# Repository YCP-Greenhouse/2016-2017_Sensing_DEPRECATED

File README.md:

# Sensing

This archive represents the efforts of the 2016-2017 capstone team.
This archive does not contain designs for the final, deployed version of the sensing system.

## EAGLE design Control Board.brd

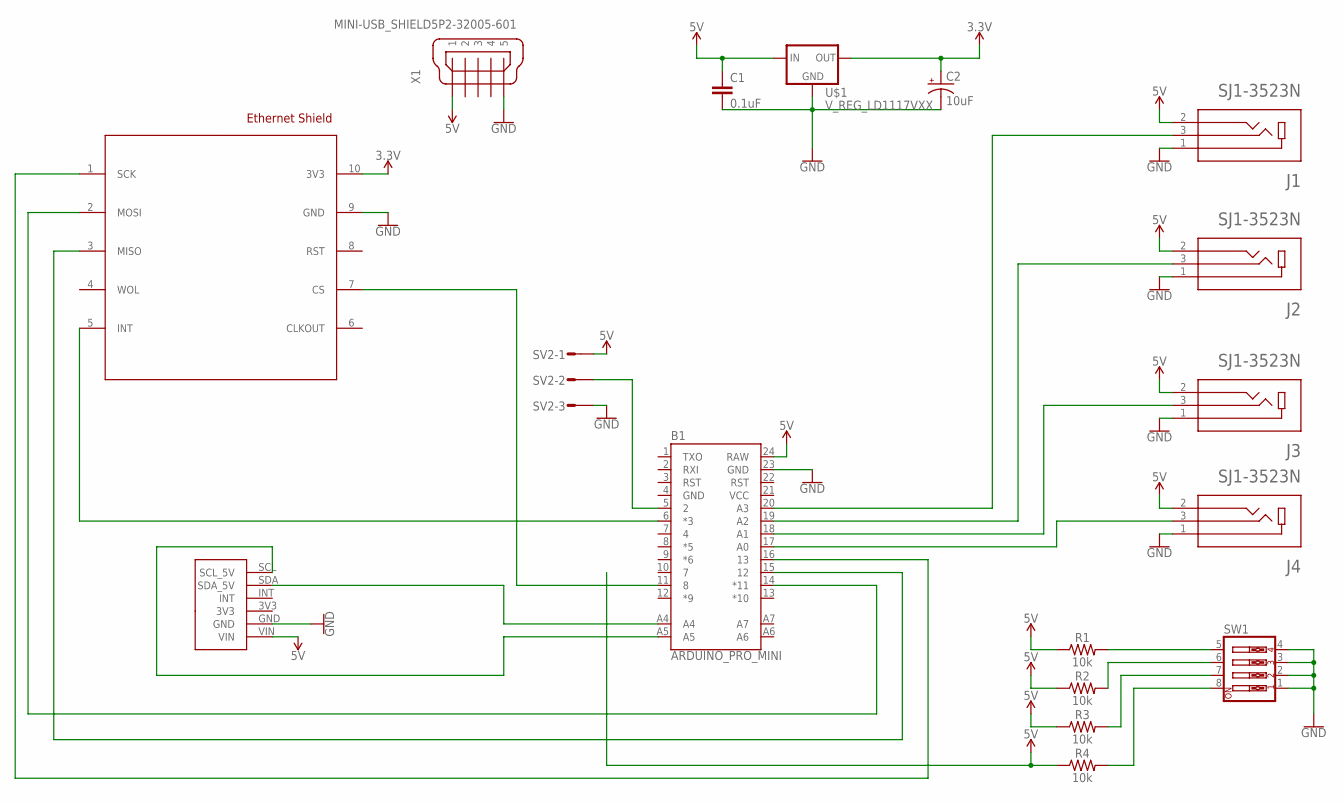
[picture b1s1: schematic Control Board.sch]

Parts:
B1: ARDUINO_PRO_MINI
C1: 0.1uF; CAP-PTH-SMALL-KIT
C2: 10uF; CPOL-RADIAL-2.5MM-5MM
J1, J2, J3, J4: SJ1-3523N; CUI_SJ1-3523N
R1, R2, R3, R4: 10k; 0603
SV2: MT6-3
SW1: SW_DIP-4; EDG-04
U$1: V_REG_LD1117VXX; 78XXL
U$2: ENC28J60-H
U$3: TSL2591
X1: MINI-USB_SHIELD5P2-32005-601; 32005-601

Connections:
3.3V: C2.1 (+), U$1.GND (OUT), U$2.10 (3V3)
5V: B1.24 (RAW), C1.1, J1.2, J2.2, J3.2, J4.2, R1.1, R2.1, R3.1, R4.1, SV2.1, U$1.OUT (IN), U$3.VIN, X1.1
GND: B1.4 (GND), B1.23 (GND), C1.2, C2.2 (-), J1.1, J2.1, J3.1, J4.1, SV2.3, SW1.1, SW1.2, SW1.3, SW1.4, U$1.IN (GND), U$2.9 (GND), U$3.GND, X1.5
unnamed: B1.5 (2), SV2.2
unnamed: B1.6 (*3), U$2.5 (INT)
unnamed: B1.20 (A3), J1.3
unnamed: B1.19 (A2), J2.3
unnamed: B1.18 (A1), J3.3
unnamed: B1.17 (A0), J4.3
unnamed: B1.16 (13), U$2.1 (SCK)
unnamed: B1.15 (12), U$2.3 (MISO)
unnamed: B1.14 (*11), U$2.2 (MOSI)
unnamed: B1.11 (8), U$2.7 (CS)
unnamed: B1.A4, U$3.SDA (SDA_5V)
unnamed: B1.A5, U$3.SCL (SCL_5V)
unnamed: R1.2, SW1.5
unnamed: R2.2, SW1.6
unnamed: R3.2, SW1.7
unnamed: R4.2, SW1.8
VCC: B1.21 (VCC)

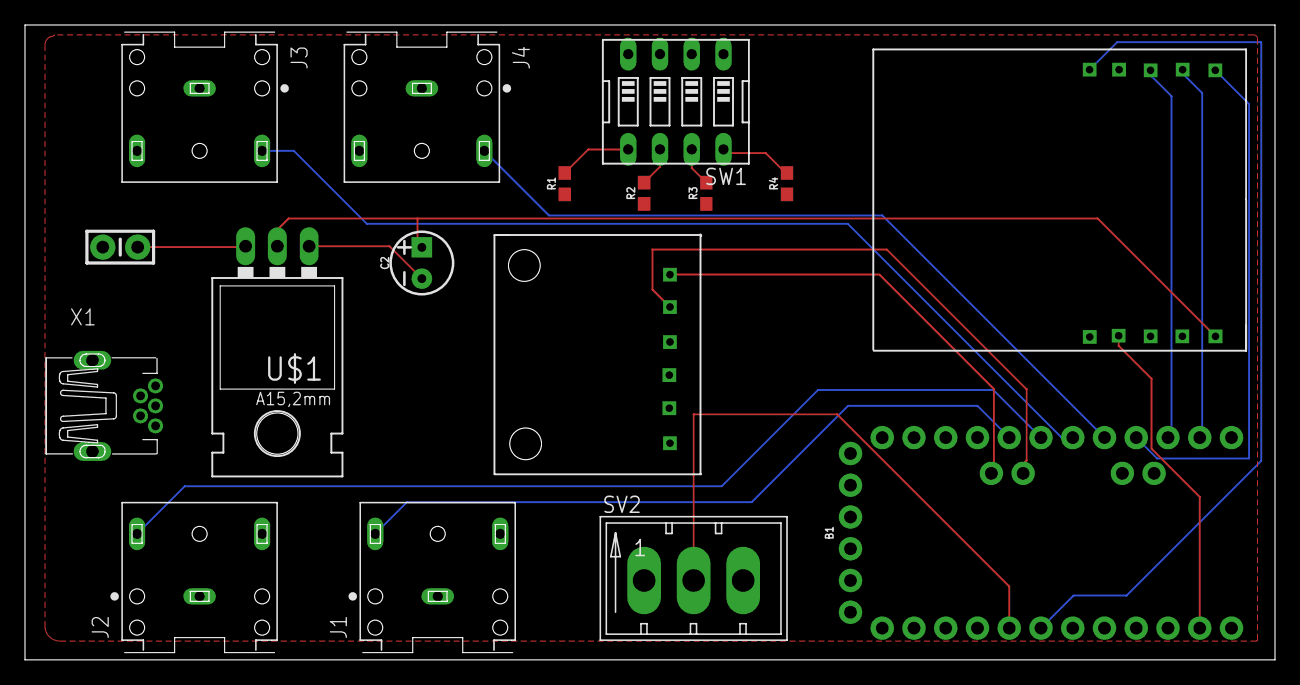
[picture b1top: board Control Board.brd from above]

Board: 2 copper layers, 100.0 x 50.8 mm, 17 parts (0 on the bottom side), 19 nets.

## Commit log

2018-05-29 Arduino code for Sensing module. Libraries are missing.
2018-06-05 PCB schematic from Newlin/O'Brien notebook
2018-06-21 Create Arduino Libraries
2018-06-28 Adding of Folders
2018-08-02 Add files via upload
    EAGLE files for Control Board
2019-03-17 Update README.md
    updated README

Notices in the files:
parts and their libraries:
SparkFun-Boards: Licensing: Creative Commons ShareAlike 4.0 International - https://creativecommons.org/licenses/by-sa/4.0
